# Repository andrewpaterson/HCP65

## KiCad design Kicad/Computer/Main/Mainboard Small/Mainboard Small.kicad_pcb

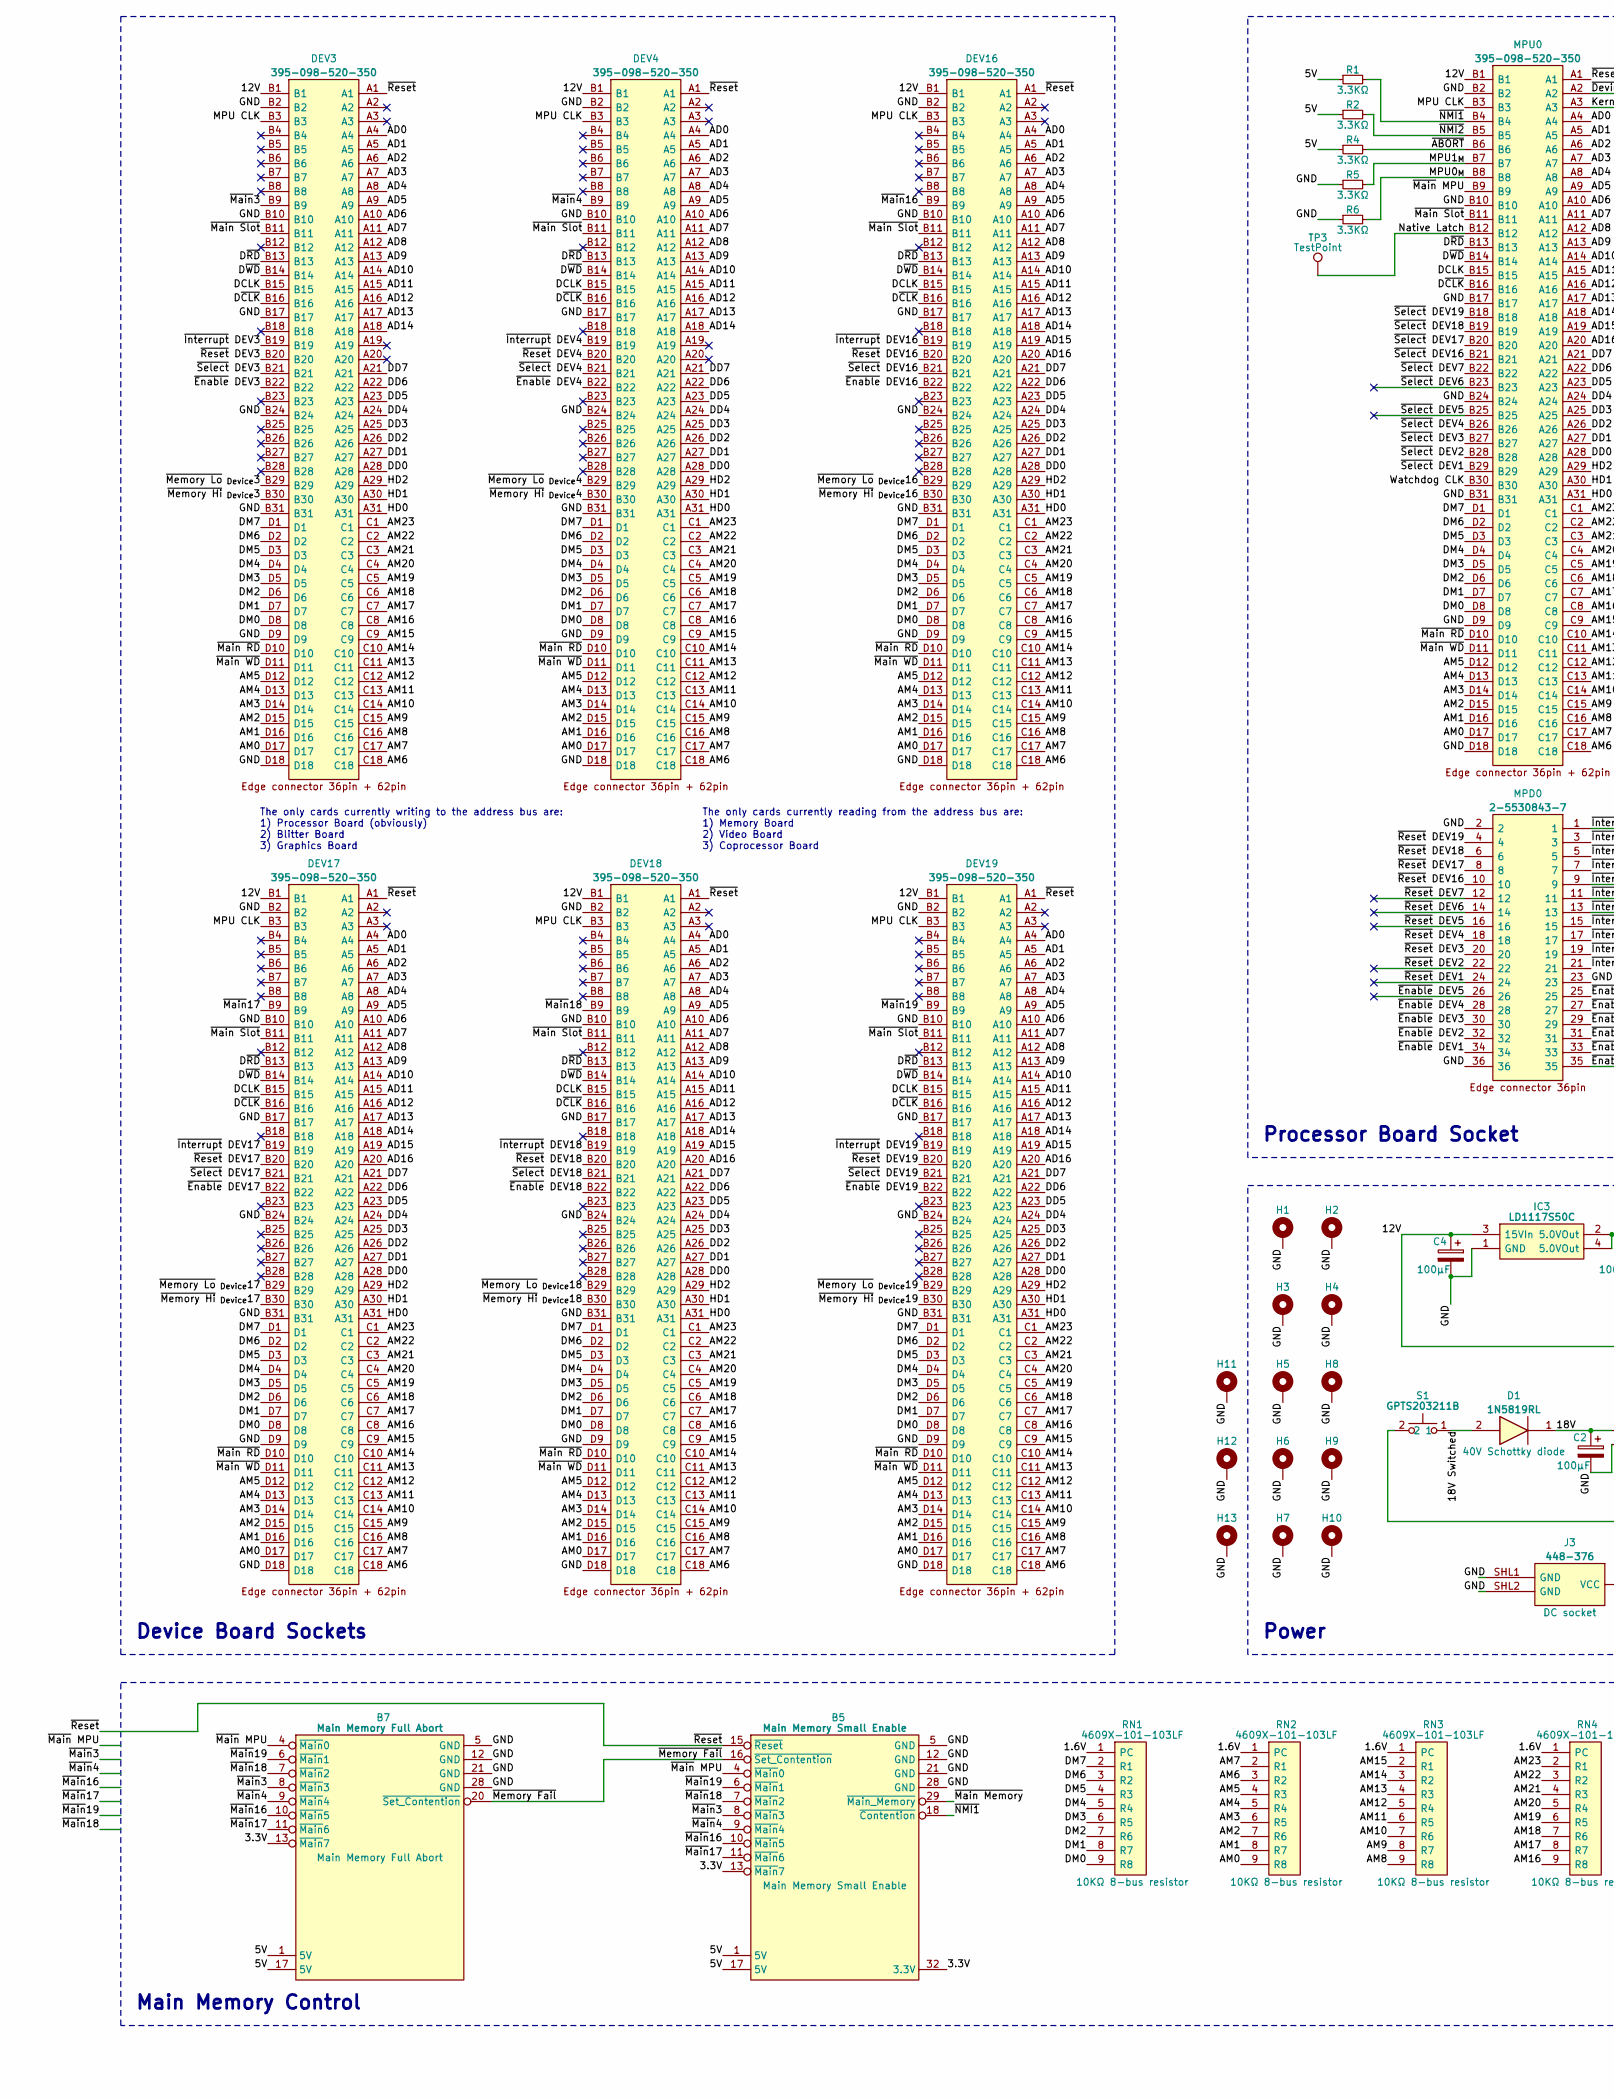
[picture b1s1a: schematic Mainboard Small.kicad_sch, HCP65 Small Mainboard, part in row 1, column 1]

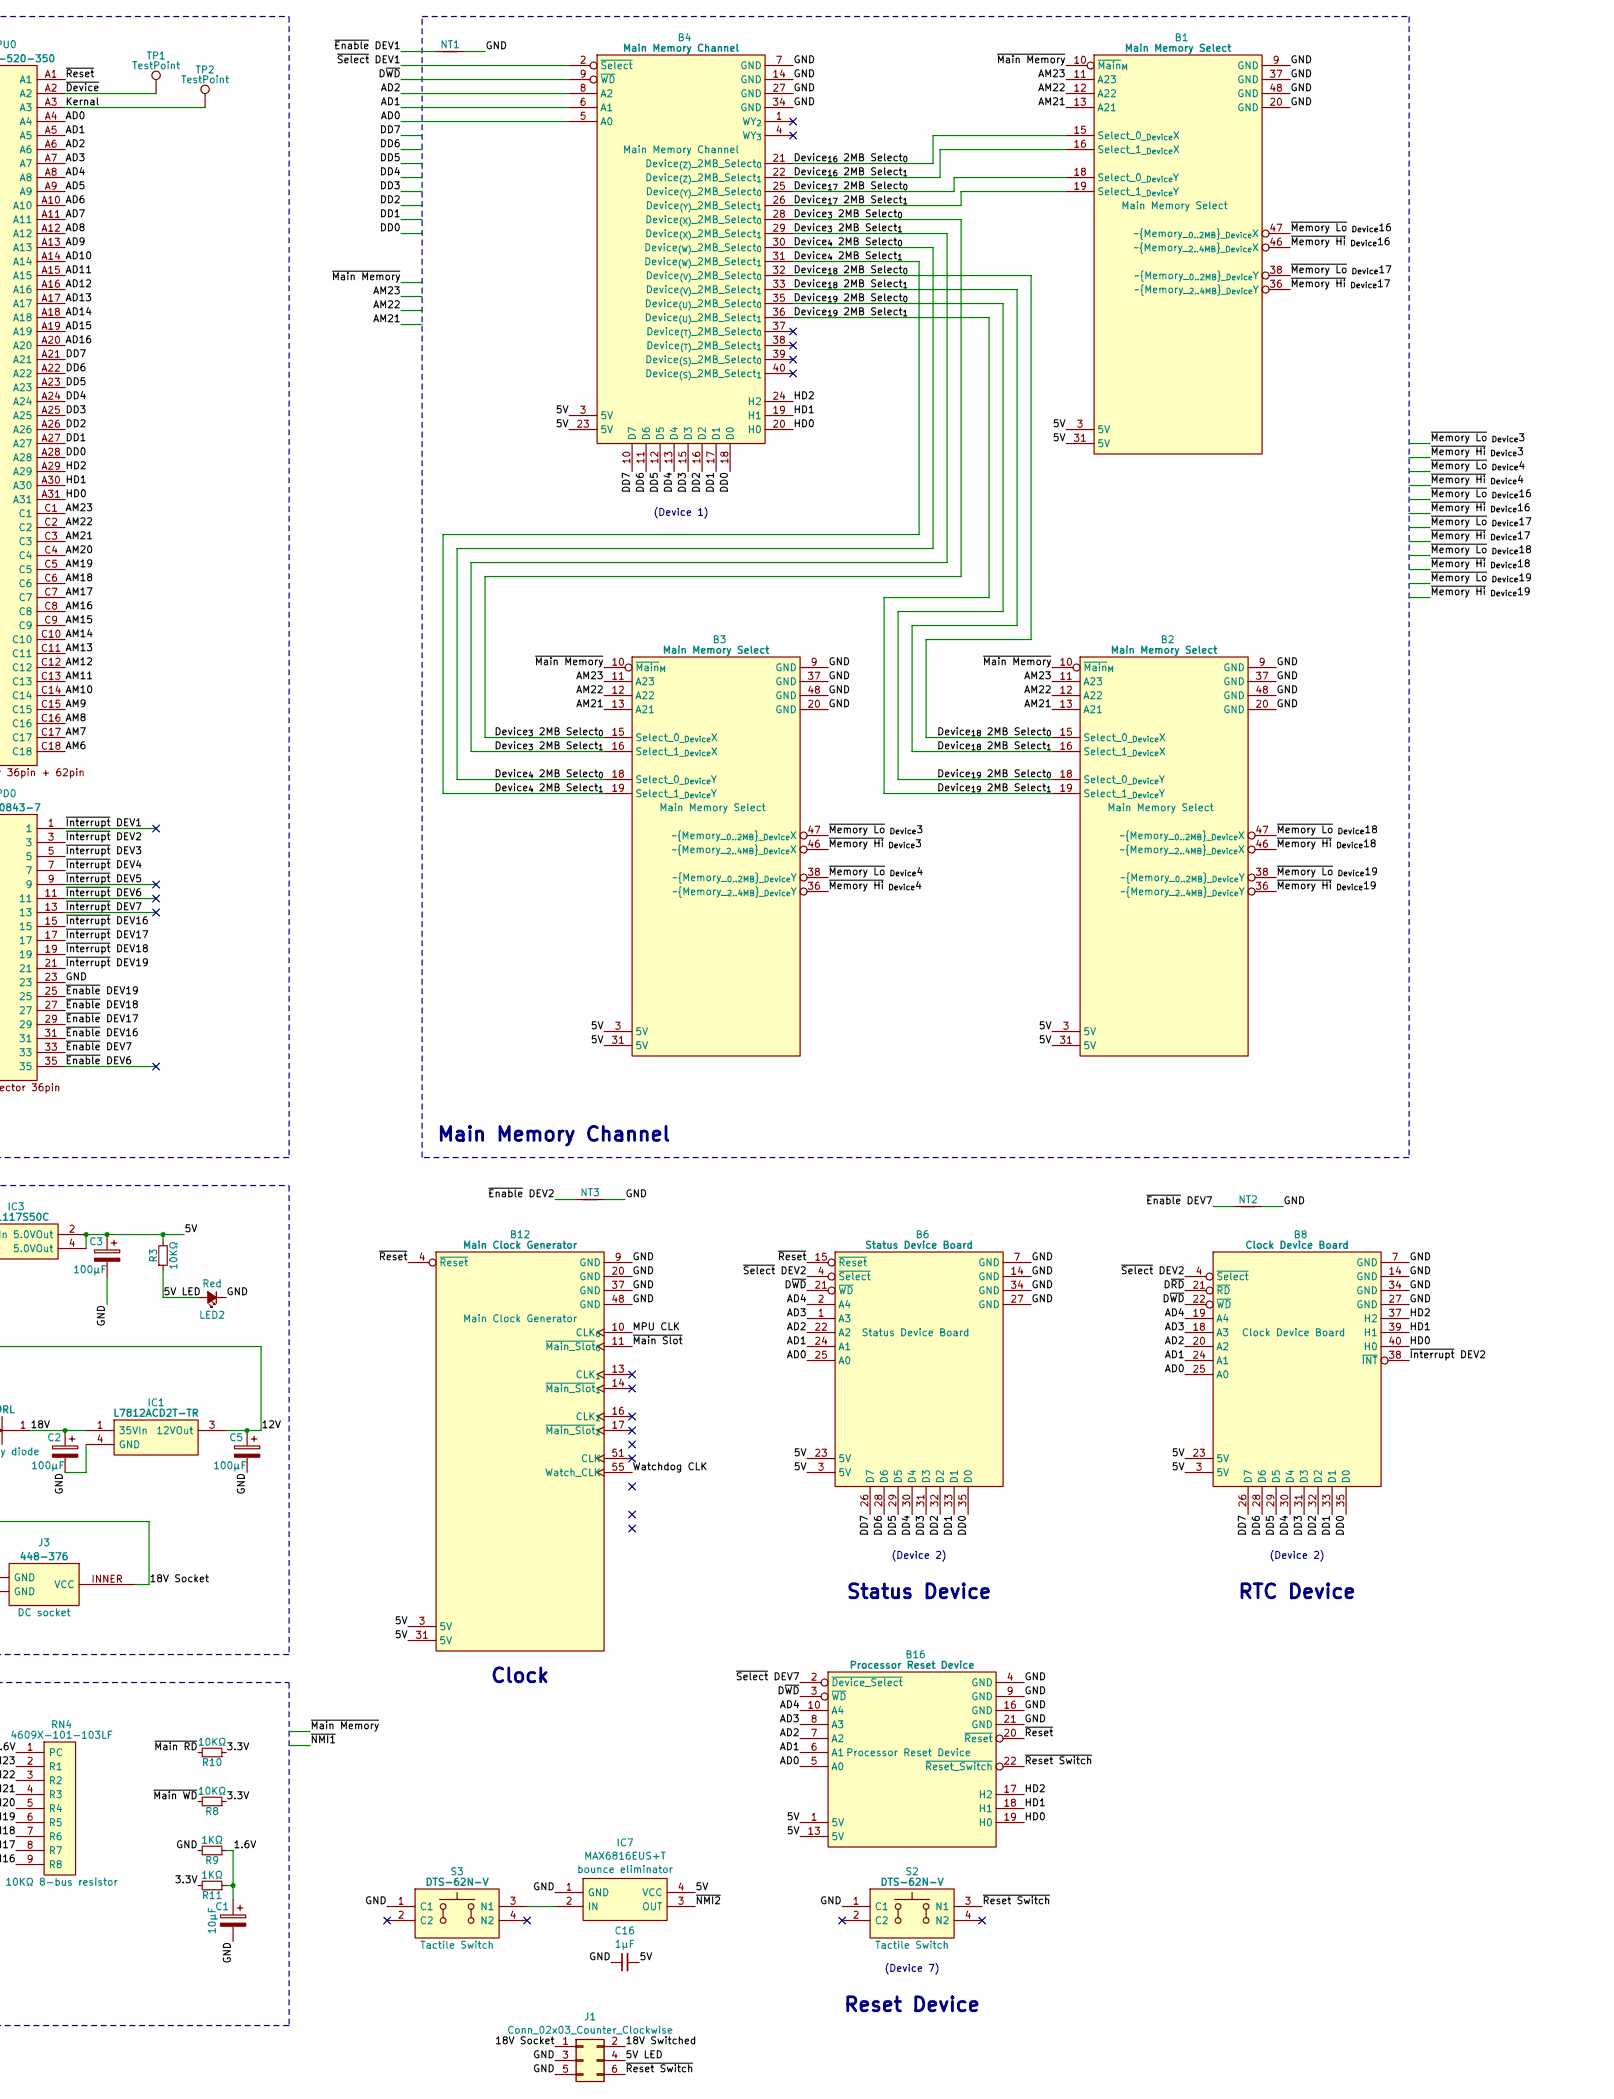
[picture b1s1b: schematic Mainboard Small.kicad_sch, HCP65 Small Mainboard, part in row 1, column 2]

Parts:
B1, B2, B3: Main Memory Select; HCP65_Main_Memory_Select
B4: Main Memory Channel; HCP65_Main_Memory_Channel
B5: Main Memory Small Enable; HCP65_Main_Memory_Small_Enable
B6: Status Device Board; HCP65_Status_Device_Board
B7: Main Memory Full Abort; HCP65_Main_Memory_Full_Abort
B8: Clock Device Board; HCP65_Clock_Device_Board
B12: Main Clock Generator; HCP65_Clock_Generator
B16: Processor Reset Device; HCP65_Processor_Reset_Device
C1: 10μF; CP_Radial_D4.0mm_P2.00mm
C2, C3, C4, C5: 100μF; CP_Radial_D6.3mm_P2.50mm
C16: 1μF; C_0805
D1: 1N5819RL; DIOAD1414W86L464D238; Manufacturer_Part_Number 1N5819RL; Mouser Part Number 511-1N5819-TR
DEV3, DEV4, DEV16, DEV17, DEV18, DEV19: 395-098-520-350; 395098520350; Manufacturer_Part_Number 395-098-520-350; Mouser Part Number 587-395-098-520-350
H1, H2, H3, H4, H5, H6, H7, H8, H9, H10, H11, H12, H13: MountingHole_Pad; HCP65_MountingHole_M3_
IC1: L7812ACD2T-TR; TO254P1542X460-3N; Manufacturer_Part_Number L7812ACD2T-TR
IC3: LD1117S50C; LD1117S33C; Manufacturer_Part_Number LD1117S50C
IC7: MAX6816EUS+T; MAX812REUST; Manufacturer_Part_Number MAX6816EUS+T; Mouser Part Number 700-MAX6816EUST
J1: Conn_02x03_Counter_Clockwise; PinHeader_2x03_P2.54mm_Vertical
J3: 448-376; 448376; Manufacturer_Part_Number 448-376
LED2: Red; LED_D5.0mm
MPD0: 2-5530843-7; 255308437; Manufacturer_Part_Number 2-5530843-7; Mouser Part Number 571-2-5530843-7
MPU0: 395-098-520-350; 395098520350; Manufacturer_Part_Number 395-098-520-350; Mouser Part Number 587-395-098-520-350
NT1, NT2, NT3: NetTie; NetTie-2_SMD_Pad0.5mm
R1, R2, R4, R5, R6: 3.3KΩ; R_0805
R3, R8, R10: 10KΩ; R_0805
R9, R11: 1KΩ; R_0805
RN1, RN2, RN3, RN4: 4609X-101-103LF; 4609X
S1: GPTS203211B; Manufacturer_Part_Number GPTS203211B; Mouser Part Number 629-GPTS203211B
S2, S3: DTS-62N-V; DTS62NV; Manufacturer_Part_Number DTS-62N-V; Mouser Part Number 113-DTS-62N-V
TP1, TP2, TP3: TestPoint; TestPoint_THTPad_2.0x2.0mm_Drill1.0mm

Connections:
/1.6V: C1.1, R9.1, R11.1, RN1.1 (PC), RN2.1 (PC), RN3.1 (PC), RN4.1 (PC)
/3.3V: B5.13 (~Main7), B5.32 (3.3V), B7.13 (~Main7), R8.1, R10.1, R11.2
/5V: B1.3 (5V), B1.31 (5V), B2.3 (5V), B2.31 (5V), B3.3 (5V), B3.31 (5V), B4.3 (5V), B4.23 (5V), B5.1 (5V), B5.17 (5V), B6.3 (5V), B6.23 (5V), B7.1 (5V), B7.17 (5V), B8.3 (5V), B8.23 (5V), B12.3 (5V), B12.31 (5V), B16.1 (5V), B16.13 (5V), C3.1, C16.2, IC3.2 (5.0VOut), IC3.4 (5.0VOut), IC7.4 (VCC), R1.1, R2.1, R3.2, R4.1
/5V LED: J1.4, LED2.2 (A), R3.1
/12V: C4.1, C5.1, DEV3.B1, DEV4.B1, DEV16.B1, DEV17.B1, DEV18.B1, DEV19.B1, IC1.3 (12VOut), IC3.3 (15VIn), MPU0.B1
/18V: C2.1, D1.1, IC1.1 (35VIn)
/18V Socket: J1.1, J3.INNER (VCC), S1.2
/18V Switched: D1.2, J1.2, S1.1
/AD0: B4.5 (A0), B6.25 (A0), B8.25 (A0), B16.5 (A0), DEV3.A4, DEV4.A4, DEV16.A4, DEV17.A4, DEV18.A4, DEV19.A4, MPU0.A4
/AD1: B4.6 (A1), B6.24 (A1), B8.24 (A1), B16.6 (A1), DEV3.A5, DEV4.A5, DEV16.A5, DEV17.A5, DEV18.A5, DEV19.A5, MPU0.A5
/AD2: B4.8 (A2), B6.22 (A2), B8.20 (A2), B16.7 (A2), DEV3.A6, DEV4.A6, DEV16.A6, DEV17.A6, DEV18.A6, DEV19.A6, MPU0.A6
/AD3: B6.1 (A3), B8.18 (A3), B16.8 (A3), DEV3.A7, DEV4.A7, DEV16.A7, DEV17.A7, DEV18.A7, DEV19.A7, MPU0.A7
/AD4: B6.2 (A4), B8.19 (A4), B16.10 (A4), DEV3.A8, DEV4.A8, DEV16.A8, DEV17.A8, DEV18.A8, DEV19.A8, MPU0.A8
/AD5: DEV3.A9, DEV4.A9, DEV16.A9, DEV17.A9, DEV18.A9, DEV19.A9, MPU0.A9
/AD6: DEV3.A10, DEV4.A10, DEV16.A10, DEV17.A10, DEV18.A10, DEV19.A10, MPU0.A10
/AD7: DEV3.A11, DEV4.A11, DEV16.A11, DEV17.A11, DEV18.A11, DEV19.A11, MPU0.A11
/AD8: DEV3.A12, DEV4.A12, DEV16.A12, DEV17.A12, DEV18.A12, DEV19.A12, MPU0.A12
/AD9: DEV3.A13, DEV4.A13, DEV16.A13, DEV17.A13, DEV18.A13, DEV19.A13, MPU0.A13
/AD10: DEV3.A14, DEV4.A14, DEV16.A14, DEV17.A14, DEV18.A14, DEV19.A14, MPU0.A14
/AD11: DEV3.A15, DEV4.A15, DEV16.A15, DEV17.A15, DEV18.A15, DEV19.A15, MPU0.A15
/AD12: DEV3.A16, DEV4.A16, DEV16.A16, DEV17.A16, DEV18.A16, DEV19.A16, MPU0.A16
/AD13: DEV3.A17, DEV4.A17, DEV16.A17, DEV17.A17, DEV18.A17, DEV19.A17, MPU0.A17
/AD14: DEV3.A18, DEV4.A18, DEV16.A18, DEV17.A18, DEV18.A18, DEV19.A18, MPU0.A18
/AD15: DEV16.A19, DEV17.A19, DEV18.A19, DEV19.A19, MPU0.A19
/AD16: DEV16.A20, DEV17.A20, DEV18.A20, DEV19.A20, MPU0.A20
/AM0: DEV3.D17, DEV4.D17, DEV16.D17, DEV17.D17, DEV18.D17, DEV19.D17, MPU0.D17, RN2.9 (R8)
/AM1: DEV3.D16, DEV4.D16, DEV16.D16, DEV17.D16, DEV18.D16, DEV19.D16, MPU0.D16, RN2.8 (R7)
/AM2: DEV3.D15, DEV4.D15, DEV16.D15, DEV17.D15, DEV18.D15, DEV19.D15, MPU0.D15, RN2.7 (R6)
/AM3: DEV3.D14, DEV4.D14, DEV16.D14, DEV17.D14, DEV18.D14, DEV19.D14, MPU0.D14, RN2.6 (R5)
/AM4: DEV3.D13, DEV4.D13, DEV16.D13, DEV17.D13, DEV18.D13, DEV19.D13, MPU0.D13, RN2.5 (R4)
/AM5: DEV3.D12, DEV4.D12, DEV16.D12, DEV17.D12, DEV18.D12, DEV19.D12, MPU0.D12, RN2.4 (R3)
/AM6: DEV3.C18, DEV4.C18, DEV16.C18, DEV17.C18, DEV18.C18, DEV19.C18, MPU0.C18, RN2.3 (R2)
/AM7: DEV3.C17, DEV4.C17, DEV16.C17, DEV17.C17, DEV18.C17, DEV19.C17, MPU0.C17, RN2.2 (R1)
/AM8: DEV3.C16, DEV4.C16, DEV16.C16, DEV17.C16, DEV18.C16, DEV19.C16, MPU0.C16, RN3.9 (R8)
/AM9: DEV3.C15, DEV4.C15, DEV16.C15, DEV17.C15, DEV18.C15, DEV19.C15, MPU0.C15, RN3.8 (R7)
/AM10: DEV3.C14, DEV4.C14, DEV16.C14, DEV17.C14, DEV18.C14, DEV19.C14, MPU0.C14, RN3.7 (R6)
/AM11: DEV3.C13, DEV4.C13, DEV16.C13, DEV17.C13, DEV18.C13, DEV19.C13, MPU0.C13, RN3.6 (R5)
/AM12: DEV3.C12, DEV4.C12, DEV16.C12, DEV17.C12, DEV18.C12, DEV19.C12, MPU0.C12, RN3.5 (R4)
/AM13: DEV3.C11, DEV4.C11, DEV16.C11, DEV17.C11, DEV18.C11, DEV19.C11, MPU0.C11, RN3.4 (R3)
/AM14: DEV3.C10, DEV4.C10, DEV16.C10, DEV17.C10, DEV18.C10, DEV19.C10, MPU0.C10, RN3.3 (R2)
/AM15: DEV3.C9, DEV4.C9, DEV16.C9, DEV17.C9, DEV18.C9, DEV19.C9, MPU0.C9, RN3.2 (R1)
/AM16: DEV3.C8, DEV4.C8, DEV16.C8, DEV17.C8, DEV18.C8, DEV19.C8, MPU0.C8, RN4.9 (R8)
/AM17: DEV3.C7, DEV4.C7, DEV16.C7, DEV17.C7, DEV18.C7, DEV19.C7, MPU0.C7, RN4.8 (R7)
/AM18: DEV3.C6, DEV4.C6, DEV16.C6, DEV17.C6, DEV18.C6, DEV19.C6, MPU0.C6, RN4.7 (R6)
/AM19: DEV3.C5, DEV4.C5, DEV16.C5, DEV17.C5, DEV18.C5, DEV19.C5, MPU0.C5, RN4.6 (R5)
/AM20: DEV3.C4, DEV4.C4, DEV16.C4, DEV17.C4, DEV18.C4, DEV19.C4, MPU0.C4, RN4.5 (R4)
/AM21: B1.13 (A21), B2.13 (A21), B3.13 (A21), DEV3.C3, DEV4.C3, DEV16.C3, DEV17.C3, DEV18.C3, DEV19.C3, MPU0.C3, RN4.4 (R3)
/AM22: B1.12 (A22), B2.12 (A22), B3.12 (A22), DEV3.C2, DEV4.C2, DEV16.C2, DEV17.C2, DEV18.C2, DEV19.C2, MPU0.C2, RN4.3 (R2)
/AM23: B1.11 (A23), B2.11 (A23), B3.11 (A23), DEV3.C1, DEV4.C1, DEV16.C1, DEV17.C1, DEV18.C1, DEV19.C1, MPU0.C1, RN4.2 (R1)
/DCLK: DEV3.B15, DEV4.B15, DEV16.B15, DEV17.B15, DEV18.B15, DEV19.B15, MPU0.B15
/DD0: B4.18 (D0), B6.35 (D0), B8.35 (D0), DEV3.A28, DEV4.A28, DEV16.A28, DEV17.A28, DEV18.A28, DEV19.A28, MPU0.A28
/DD1: B4.17 (D1), B6.33 (D1), B8.33 (D1), DEV3.A27, DEV4.A27, DEV16.A27, DEV17.A27, DEV18.A27, DEV19.A27, MPU0.A27
/DD2: B4.16 (D2), B6.32 (D2), B8.32 (D2), DEV3.A26, DEV4.A26, DEV16.A26, DEV17.A26, DEV18.A26, DEV19.A26, MPU0.A26
/DD3: B4.15 (D3), B6.31 (D3), B8.31 (D3), DEV3.A25, DEV4.A25, DEV16.A25, DEV17.A25, DEV18.A25, DEV19.A25, MPU0.A25
/DD4: B4.13 (D4), B6.30 (D4), B8.30 (D4), DEV3.A24, DEV4.A24, DEV16.A24, DEV17.A24, DEV18.A24, DEV19.A24, MPU0.A24
/DD5: B4.12 (D5), B6.29 (D5), B8.29 (D5), DEV3.A23, DEV4.A23, DEV16.A23, DEV17.A23, DEV18.A23, DEV19.A23, MPU0.A23
/DD6: B4.11 (D6), B6.28 (D6), B8.28 (D6), DEV3.A22, DEV4.A22, DEV16.A22, DEV17.A22, DEV18.A22, DEV19.A22, MPU0.A22
/DD7: B4.10 (D7), B6.26 (D7), B8.26 (D7), DEV3.A21, DEV4.A21, DEV16.A21, DEV17.A21, DEV18.A21, DEV19.A21, MPU0.A21
/DM0: DEV3.D8, DEV4.D8, DEV16.D8, DEV17.D8, DEV18.D8, DEV19.D8, MPU0.D8, RN1.9 (R8)
/DM1: DEV3.D7, DEV4.D7, DEV16.D7, DEV17.D7, DEV18.D7, DEV19.D7, MPU0.D7, RN1.8 (R7)
/DM2: DEV3.D6, DEV4.D6, DEV16.D6, DEV17.D6, DEV18.D6, DEV19.D6, MPU0.D6, RN1.7 (R6)
/DM3: DEV3.D5, DEV4.D5, DEV16.D5, DEV17.D5, DEV18.D5, DEV19.D5, MPU0.D5, RN1.6 (R5)
/DM4: DEV3.D4, DEV4.D4, DEV16.D4, DEV17.D4, DEV18.D4, DEV19.D4, MPU0.D4, RN1.5 (R4)
/DM5: DEV3.D3, DEV4.D3, DEV16.D3, DEV17.D3, DEV18.D3, DEV19.D3, MPU0.D3, RN1.4 (R3)
/DM6: DEV3.D2, DEV4.D2, DEV16.D2, DEV17.D2, DEV18.D2, DEV19.D2, MPU0.D2, RN1.3 (R2)
/DM7: DEV3.D1, DEV4.D1, DEV16.D1, DEV17.D1, DEV18.D1, DEV19.D1, MPU0.D1, RN1.2 (R1)
/Device_{3} 2MB Select_{0}: B3.15 (Select_0_{_Device}X), B4.28 (Device_{(X)}_2MB_Select_{0})
/Device_{3} 2MB Select_{1}: B3.16 (Select_1_{_Device}X), B4.29 (Device_{(X)}_2MB_Select_{1})
/Device_{4} 2MB Select_{0}: B3.18 (Select_0_{_Device}Y), B4.30 (Device_{(W)}_2MB_Select_{0})
/Device_{4} 2MB Select_{1}: B3.19 (Select_1_{_Device}Y), B4.31 (Device_{(W)}_2MB_Select_{1})
/Device_{16} 2MB Select_{0}: B1.15 (Select_0_{_Device}X), B4.21 (Device_{(Z)}_2MB_Select_{0})
/Device_{16} 2MB Select_{1}: B1.16 (Select_1_{_Device}X), B4.22 (Device_{(Z)}_2MB_Select_{1})
/Device_{17} 2MB Select_{0}: B1.18 (Select_0_{_Device}Y), B4.25 (Device_{(Y)}_2MB_Select_{0})
/Device_{17} 2MB Select_{1}: B1.19 (Select_1_{_Device}Y), B4.26 (Device_{(Y)}_2MB_Select_{1})
/Device_{18} 2MB Select_{0}: B2.15 (Select_0_{_Device}X), B4.32 (Device_{(V)}_2MB_Select_{0})
/Device_{18} 2MB Select_{1}: B2.16 (Select_1_{_Device}X), B4.33 (Device_{(V)}_2MB_Select_{1})
/Device_{19} 2MB Select_{0}: B2.18 (Select_0_{_Device}Y), B4.35 (Device_{(U)}_2MB_Select_{0})
/Device_{19} 2MB Select_{1}: B2.19 (Select_1_{_Device}Y), B4.36 (Device_{(U)}_2MB_Select_{1})
/D~CLK: DEV3.B16, DEV4.B16, DEV16.B16, DEV17.B16, DEV18.B16, DEV19.B16, MPU0.B16
/D~RD: B8.21 (~RD), DEV3.B13, DEV4.B13, DEV16.B13, DEV17.B13, DEV18.B13, DEV19.B13, MPU0.B13
/D~WD: B4.9 (~WD), B6.21 (~WD), B8.22 (~WD), B16.3 (~WD), DEV3.B14, DEV4.B14, DEV16.B14, DEV17.B14, DEV18.B14, DEV19.B14, MPU0.B14
/GND: B1.9 (GND), B1.20 (GND), B1.37 (GND), B1.48 (GND), B2.9 (GND), B2.20 (GND), B2.37 (GND), B2.48 (GND), B3.9 (GND), B3.20 (GND), B3.37 (GND), B3.48 (GND), B4.7 (GND), B4.14 (GND), B4.27 (GND), B4.34 (GND), B5.5 (GND), B5.12 (GND), B5.21 (GND), B5.28 (GND), B6.7 (GND), B6.14 (GND), B6.27 (GND), B6.34 (GND), B7.5 (GND), B7.12 (GND), B7.21 (GND), B7.28 (GND), B8.7 (GND), B8.14 (GND), B8.27 (GND), B8.34 (GND), B12.9 (GND), B12.20 (GND), B12.37 (GND), B12.48 (GND), B16.4 (GND), B16.9 (GND), B16.16 (GND), B16.21 (GND), C1.2, C2.2, C3.2, C4.2, C5.2, C16.1, DEV3.B2, DEV3.B10, DEV3.B17, DEV3.B24, DEV3.B31, DEV3.D9, DEV3.D18, DEV4.B2, DEV4.B10, DEV4.B17, DEV4.B24, DEV4.B31, DEV4.D9, DEV4.D18, DEV16.B2, DEV16.B10, DEV16.B17, DEV16.B24, DEV16.B31, DEV16.D9, DEV16.D18, DEV17.B2, DEV17.B10, DEV17.B17, DEV17.B24, DEV17.B31, DEV17.D9, DEV17.D18, DEV18.B2, DEV18.B10, DEV18.B17, DEV18.B24, DEV18.B31, DEV18.D9, DEV18.D18, DEV19.B2, DEV19.B10, DEV19.B17, DEV19.B24, DEV19.B31, DEV19.D9, DEV19.D18, H1.1 (GND_1), H2.1 (GND_1), H3.1 (GND_1), H4.1 (GND_1), H5.1 (GND_1), H6.1 (GND_1), H7.1 (GND_1), H8.1 (GND_1), H9.1 (GND_1), H10.1 (GND_1), H11.1 (GND_1), H12.1 (GND_1), H13.1 (GND_1), IC1.4 (GND), IC3.1 (GND), IC7.1 (GND), J1.3, J1.5, J3.SHL1 (GND), J3.SHL2 (GND), LED2.1 (K), MPD0.2, MPD0.23, MPD0.36, MPU0.B2, MPU0.B10, MPU0.B17, MPU0.B24, MPU0.B31, MPU0.D9, MPU0.D18, NT1.2, NT2.2, NT3.2, R5.1, R6.1, R9.2, S2.1 (C1), S3.1 (C1)
/HD0: B4.20 (H0), B8.40 (H0), B16.19 (H0), DEV3.A31, DEV4.A31, DEV16.A31, DEV17.A31, DEV18.A31, DEV19.A31, MPU0.A31
/HD1: B4.19 (H1), B8.39 (H1), B16.18 (H1), DEV3.A30, DEV4.A30, DEV16.A30, DEV17.A30, DEV18.A30, DEV19.A30, MPU0.A30
/HD2: B4.24 (H2), B8.37 (H2), B16.17 (H2), DEV3.A29, DEV4.A29, DEV16.A29, DEV17.A29, DEV18.A29, DEV19.A29, MPU0.A29
/Kernal: MPU0.A3, TP2.1 (1_1)
/MPU0_{M}: MPU0.B8, R6.2
/MPU1_{M}: MPU0.B7, R5.2
/MPU CLK: B12.10 (CLK_{0}), DEV3.B3, DEV4.B3, DEV16.B3, DEV17.B3, DEV18.B3, DEV19.B3, MPU0.B3
/Native Latch: MPU0.B12, TP3.1 (1_1)
/Watchdog CLK: B12.55 (Watch_CLK), MPU0.B30
/~ABORT: MPU0.B6, R4.2
/~Device: MPU0.A2, TP1.1 (1_1)
/~Enable DEV1: MPD0.34, NT1.1
/~Enable DEV2: MPD0.32, NT3.1
/~Enable DEV3: DEV3.B22, MPD0.30
/~Enable DEV4: DEV4.B22, MPD0.28
/~Enable DEV5: MPD0.26
/~Enable DEV6: MPD0.35
/~Enable DEV7: MPD0.33, NT2.1
/~Enable DEV16: DEV16.B22, MPD0.31
/~Enable DEV17: DEV17.B22, MPD0.29
/~Enable DEV18: DEV18.B22, MPD0.27
/~Enable DEV19: DEV19.B22, MPD0.25
/~Interrupt DEV1: MPD0.1
/~Interrupt DEV2: B8.38 (~INT), MPD0.3
/~Interrupt DEV3: DEV3.B19, MPD0.5
/~Interrupt DEV4: DEV4.B19, MPD0.7
/~Interrupt DEV5: MPD0.9
/~Interrupt DEV6: MPD0.11
/~Interrupt DEV7: MPD0.13
/~Interrupt DEV16: DEV16.B19, MPD0.15
/~Interrupt DEV17: DEV17.B19, MPD0.17
/~Interrupt DEV18: DEV18.B19, MPD0.19
/~Interrupt DEV19: DEV19.B19, MPD0.21
/~Main Memory: B1.10 (~Main_{M}), B2.10 (~Main_{M}), B3.10 (~Main_{M}), B5.29 (~Main_Memory)
/~Main RD: DEV3.D10, DEV4.D10, DEV16.D10, DEV17.D10, DEV18.D10, DEV19.D10, MPU0.D10, R10.2
/~Main Slot: B12.11 (~Main_Slot_{0}), DEV3.B11, DEV4.B11, DEV16.B11, DEV17.B11, DEV18.B11, DEV19.B11, MPU0.B11
/~Main WD: DEV3.D11, DEV4.D11, DEV16.D11, DEV17.D11, DEV18.D11, DEV19.D11, MPU0.D11, R8.2
/~Main3: B5.8 (~Main3), B7.8 (~Main3), DEV3.B9
/~Main4: B5.9 (~Main4), B7.9 (~Main4), DEV4.B9
/~Main16: B5.10 (~Main5), B7.10 (~Main5), DEV16.B9
/~Main17: B5.11 (~Main6), B7.11 (~Main6), DEV17.B9
/~Main18: B5.7 (~Main2), B7.7 (~Main2), DEV18.B9
/~Main19: B5.6 (~Main1), B7.6 (~Main1), DEV19.B9
/~Main MPU: B5.4 (~Main0), B7.4 (~Main0), MPU0.B9
/~Memory Fail: B5.16 (~Set_Contention), B7.20 (~Set_Contention)
/~Memory Hi_{ Device}3: B3.46 (~Memory__{2..4MB}_{_Device}X), DEV3.B30
/~Memory Hi_{ Device}4: B3.36 (~Memory__{2..4MB}_{_Device}Y), DEV4.B30
/~Memory Hi_{ Device}16: B1.46 (~Memory__{2..4MB}_{_Device}X), DEV16.B30
/~Memory Hi_{ Device}17: B1.36 (~Memory__{2..4MB}_{_Device}Y), DEV17.B30
/~Memory Hi_{ Device}18: B2.46 (~Memory__{2..4MB}_{_Device}X), DEV18.B30
/~Memory Hi_{ Device}19: B2.36 (~Memory__{2..4MB}_{_Device}Y), DEV19.B30
/~Memory Lo_{ Device}3: B3.47 (~Memory__{0..2MB}_{_Device}X), DEV3.B29
/~Memory Lo_{ Device}4: B3.38 (~Memory__{0..2MB}_{_Device}Y), DEV4.B29
/~Memory Lo_{ Device}16: B1.47 (~Memory__{0..2MB}_{_Device}X), DEV16.B29
/~Memory Lo_{ Device}17: B1.38 (~Memory__{0..2MB}_{_Device}Y), DEV17.B29
/~Memory Lo_{ Device}18: B2.47 (~Memory__{0..2MB}_{_Device}X), DEV18.B29
/~Memory Lo_{ Device}19: B2.38 (~Memory__{0..2MB}_{_Device}Y), DEV19.B29
/~NMI1: B5.18 (~Contention), MPU0.B4, R1.2
/~NMI2: IC7.3 (OUT), MPU0.B5, R2.2
/~Reset Switch: B16.22 (~Reset_Switch), J1.6, S2.3 (N1)
/~Reset: B5.15 (~Reset), B6.15 (~Reset), B12.4 (~Reset), B16.20 (~Reset), DEV3.A1, DEV4.A1, DEV16.A1, DEV17.A1, DEV18.A1, DEV19.A1, MPU0.A1
/~Reset DEV1: MPD0.24
/~Reset DEV2: MPD0.22
/~Reset DEV3: DEV3.B20, MPD0.20
/~Reset DEV4: DEV4.B20, MPD0.18
/~Reset DEV5: MPD0.16
/~Reset DEV6: MPD0.14
/~Reset DEV7: MPD0.12
/~Reset DEV16: DEV16.B20, MPD0.10
/~Reset DEV17: DEV17.B20, MPD0.8
/~Reset DEV18: DEV18.B20, MPD0.6
/~Reset DEV19: DEV19.B20, MPD0.4
/~Select DEV1: B4.2 (~Select), MPU0.B29
/~Select DEV2: B6.4 (~Select), B8.4 (~Select), MPU0.B28
/~Select DEV3: DEV3.B21, MPU0.B27
/~Select DEV4: DEV4.B21, MPU0.B26
/~Select DEV5: MPU0.B25
/~Select DEV6: MPU0.B23
/~Select DEV7: B16.2 (~Device_Select), MPU0.B22
/~Select DEV16: DEV16.B21, MPU0.B21
/~Select DEV17: DEV17.B21, MPU0.B20
/~Select DEV18: DEV18.B21, MPU0.B19
/~Select DEV19: DEV19.B21, MPU0.B18
unnamed: IC7.2 (IN), S3.3 (N1)

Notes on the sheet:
RTC Device
Clock
(Device 1)
Processor Board Socket
Power
Main Memory Control
The only cards currently writing to the address bus are: 1) Processor Board (obviously) 2) Blitter Board 3) Graphics Board
(Device 2)
(Device 7)
The only cards currently reading from the address bus are: 1) Memory Board 2) Video Board 3) Coprocessor Board
Main Memory Channel
Status Device
Device Board Sockets
Reset Device

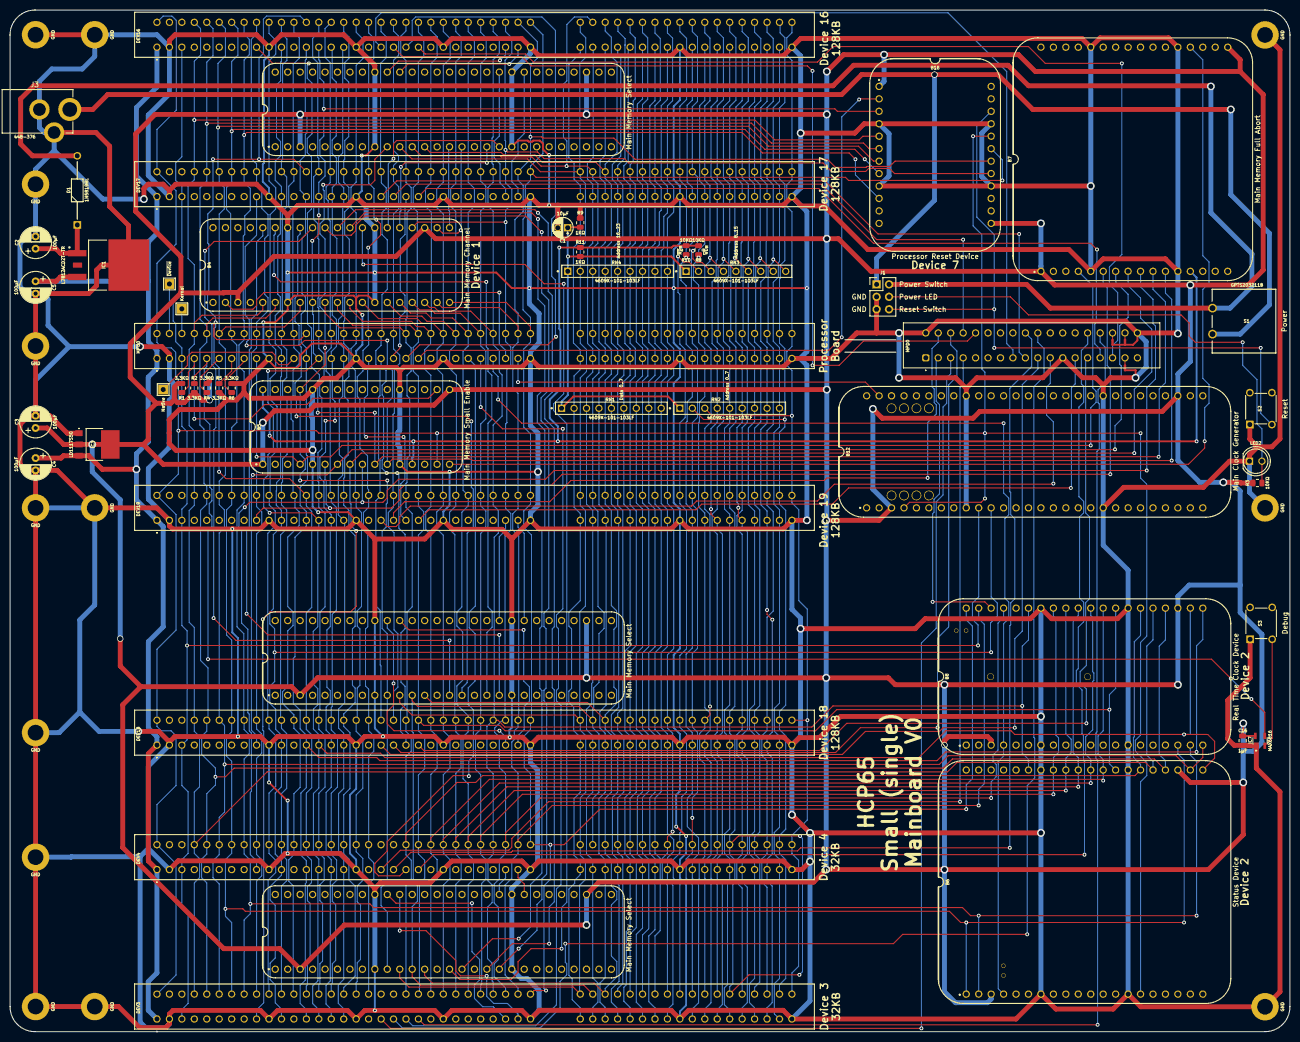
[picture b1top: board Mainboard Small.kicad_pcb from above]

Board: 2 copper layers, 261.1 x 208.4 mm, 67 parts (0 on the bottom side), 153 nets.
